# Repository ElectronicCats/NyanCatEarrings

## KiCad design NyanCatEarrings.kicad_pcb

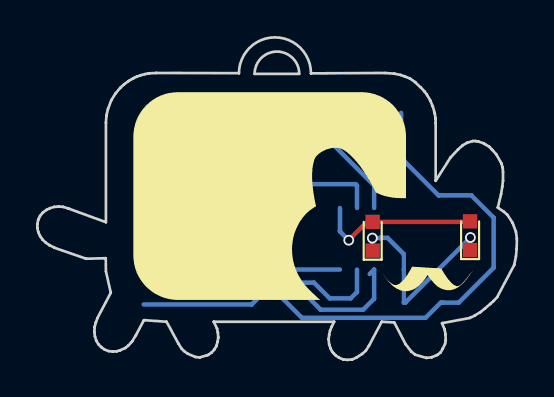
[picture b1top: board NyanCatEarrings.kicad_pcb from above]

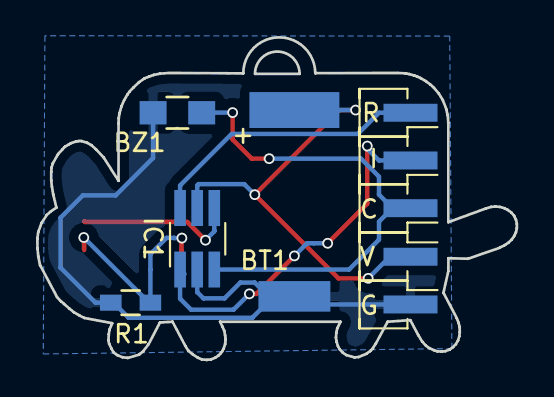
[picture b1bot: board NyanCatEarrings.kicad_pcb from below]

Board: 2 copper layers, 26.6 x 17.9 mm, 12 parts (9 on the bottom side), 7 nets.

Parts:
BT1: Battery_Cell; Supercapcoin
BZ1: Buzzer; R_0805_HandSoldering
D1, D2: LED; LED_0603
IC1: ATTINY10-TS; TSOT-23-6_MK06A_HandSoldering
P1: G; Pin_Header_Straight_1x01_Pitch2.54mm_SMD_Pin1Right
P2: V; Pin_Header_Straight_1x01_Pitch2.54mm_SMD_Pin1Right
P4: I; Pin_Header_Straight_1x01_Pitch2.54mm_SMD_Pin1Left
P5: C; Pin_Header_Straight_1x01_Pitch2.54mm_SMD_Pin1Left
P6: R; Pin_Header_Straight_1x01_Pitch2.54mm_SMD_Pin1Left
R1: 100; R_0603_HandSoldering
svg2mod: G***; NyanCat

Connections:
GND: BT1.2, BZ1.2, IC1.2, P1.1, R1.2
unnamed: BT1.1, IC1.5, P2.1
unnamed: BZ1.1, IC1.3, P5.1
unnamed: D1.1, D2.1, R1.1
unnamed: D1.2, D2.2, IC1.4
unnamed: IC1.1, P4.1
unnamed: IC1.6, P6.1

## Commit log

2017-08-30 add gitignore
2017-09-10 Version panel
2017-09-10 Update gitignore
2017-09-10 upload gerbers
2017-09-10 Update PCB
2018-03-10 Update best render
2018-03-10 Update BOM
2018-03-10 Update supercapacitor
2018-03-11 Optimized tracks
